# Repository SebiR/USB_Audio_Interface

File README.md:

# USB Audio Interface with Line In or Out
A very compact USB sound card with either two line inputs or two line outputs

## Features
* USB-C connector (USB 1.1 standard)
* Can be set to Line Out or Line In with solder jumpers
* The front plate can be flipped for Input or Output labeling
* Bus powered
* With PCB front plates no mechanical work is neccessary (except for some countersinking)

# Inner Workings

The main chip of the audio interface is a PCM2904 from Texas Instruments. It has an in- and output capability of 16bit at 48kHz, enough for most applications.
A high-quality OPA2523 op amp is used as a low-pass filter to get rid of high frequency noise. It's basically a copy of the PCM2902 eval board from TI.

On the underside, there are six SMT solder jumpers. Four of them determine the direction of the input/output LPF, so configuring the device as a Line In or a Line out device.
In case of a Line out configuration, the two inputs can be tied to GND to avoid any noise.

# Case

The PCB and the front plates are designed to fit inside ultra small Hammond 1455D601 metal case.
But if you want to save ~15€, you can download the 3D CAD files for the case and print it for yourself:
https://www.hammfg.com/part/1455D601

Although a nice anodized aluminum case is pretty nifty!

# Maybe?
It would be really nice to be able to change the direction mid-operation, but that would require some analog switches. Maybe I'll create another version somewhere in the future

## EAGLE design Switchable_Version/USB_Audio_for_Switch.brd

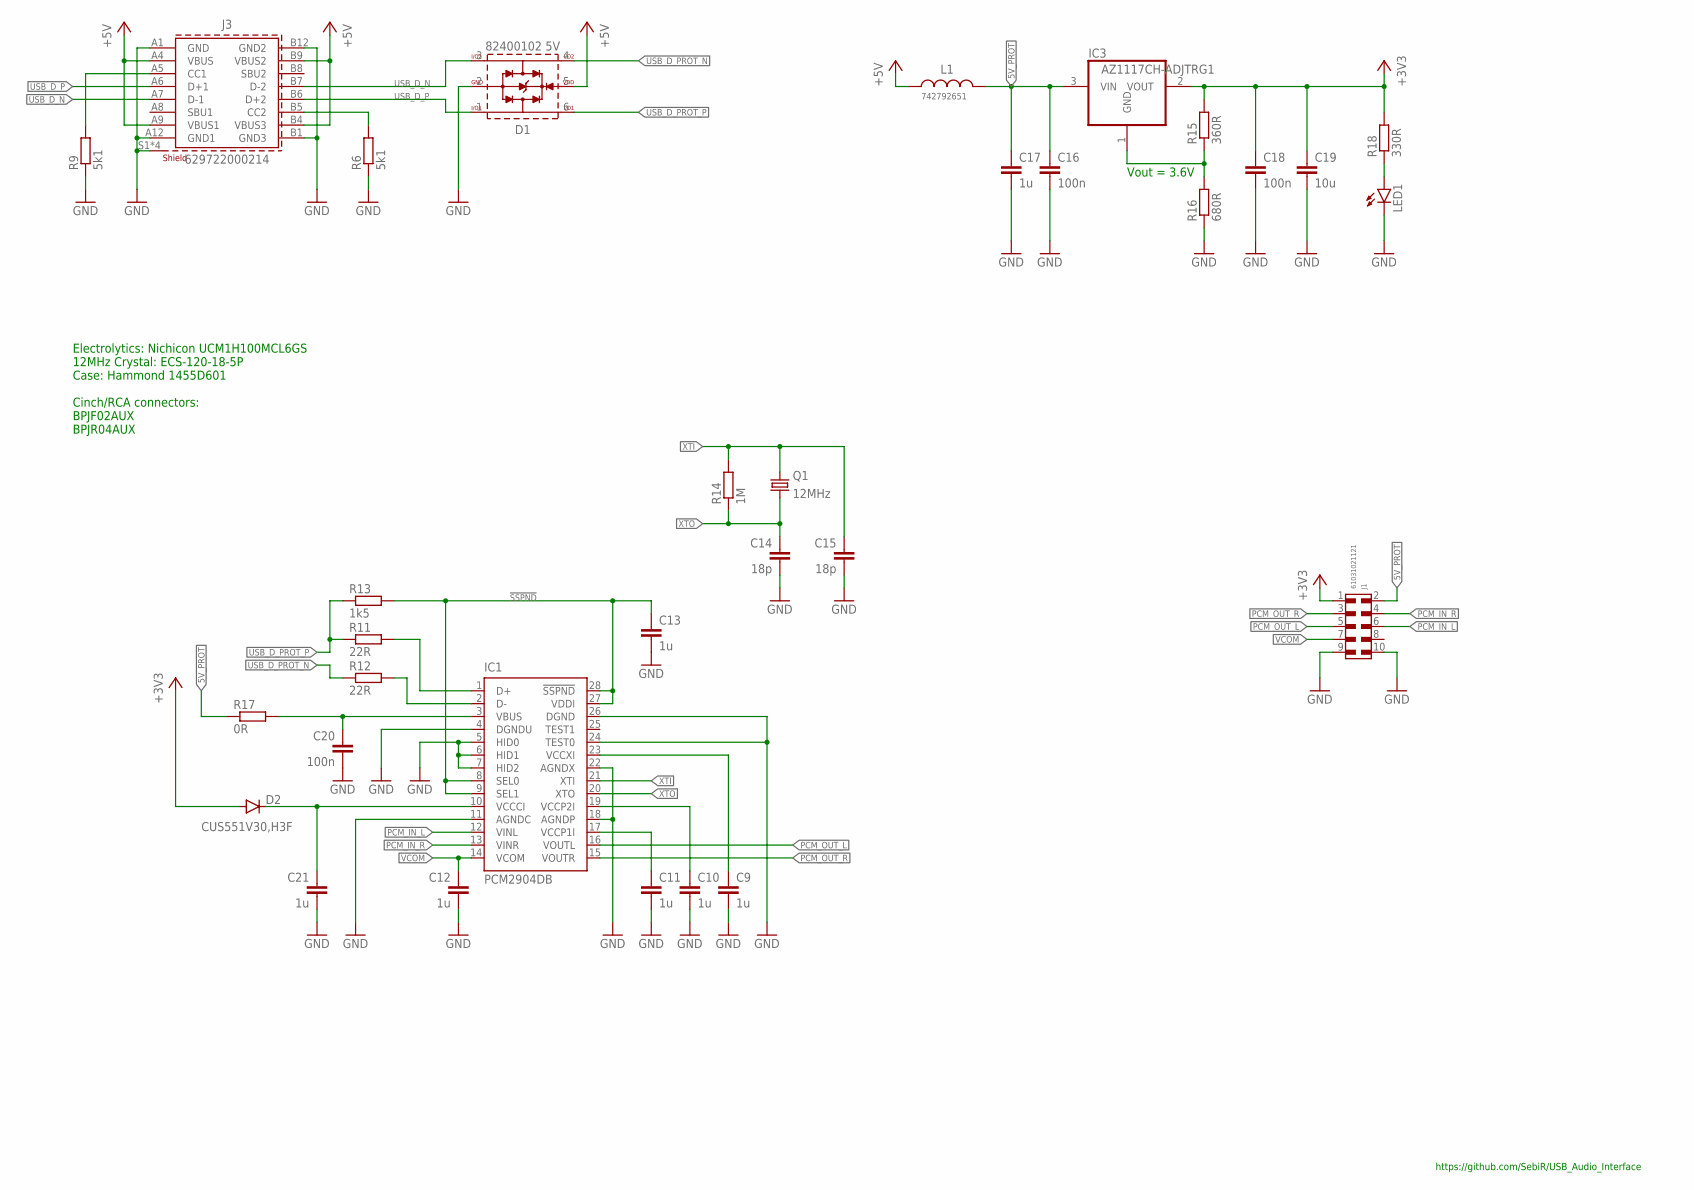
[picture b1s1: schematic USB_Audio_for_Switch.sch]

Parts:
C9, C10, C11, C12, C13, C17, C21: 1u; C0603
C14, C15: 18p; C0603
C16, C18, C20: 100n; C0603
C19: 10u; C0603
D1: 82400102 5V; WE-TVS_SOT23-6L
D2: CUS551V30,H3F; SOD323-R
IC1: PCM2904DB; SSOP28DB
IC3: AZ1117CH-ADJTRG1; SOT223
J1: 61031021121
J3: 629722000214
L1: 742792651; WE-CBF_0603_W2.6
LED1: LEDMICRO-SIDELED; MICRO-SIDELED
Q1: 12MHz; HC49UP
R6, R9: 5k1; R0603
R11, R12: 22R; R0603
R13: 1k5; R0603
R14: 1M; R0603
R15: 360R; R0603
R16: 680R; R0603
R17: 0R; R0603
R18: 330R; R0603

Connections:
5V_PROT: C16.1, C17.1, IC3.3 (VIN), J1.2, L1.2, R17.1
!SSPND: C13.1, IC1.8 (SEL0), IC1.9 (SEL1), IC1.27 (VDDI), IC1.28 (!SSPND), R13.2
+3V3: C18.1, C19.1, D2.A, IC3.2 (VOUT), J1.1, R15.2, R18.2
+5V: D1.5 (VDD), J3.A4 (VBUS), J3.A9 (VBUS1), J3.B4 (VBUS3), J3.B9 (VBUS2), L1.1
GND: C9.2, C10.2, C11.2, C12.2, C13.2, C14.2, C15.2, C16.2, C17.2, C18.2, C19.2, C20.2, C21.2, D1.2 (GND), IC1.4 (DGNDU), IC1.5 (HID0), IC1.6 (HID1), IC1.7 (HID2), IC1.11 (AGNDC), IC1.18 (AGNDP), IC1.22 (AGNDX), IC1.24 (TEST0), IC1.26 (DGND), J1.9, J1.10, J3.A1 (GND), J3.A12 (GND1), J3.B1 (GND3), J3.B12 (GND2), J3.S1 (SHIELD), J3.S2 (SHIELD), J3.S3 (SHIELD), J3.S4 (SHIELD), LED1.C, R6.1, R9.1, R16.1
unnamed: J3.A5 (CC1), R9.2
unnamed: J3.B5 (CC2), R6.2
unnamed: IC3.1 (GND), R15.1, R16.2
unnamed: LED1.A, R18.1
unnamed: C20.1, IC1.3 (VBUS), R17.2
unnamed: C9.1, IC1.23 (VCCXI)
unnamed: C11.1, IC1.17 (VCCP1I)
unnamed: C10.1, IC1.19 (VCCP2I)
unnamed: C21.1, D2.C, IC1.10 (VCCCI)
PCM_IN_L: IC1.12 (VINL), J1.6
PCM_IN_R: IC1.13 (VINR), J1.4
PCM_OUT_L: IC1.16 (VOUTL), J1.5
PCM_OUT_R: IC1.15 (VOUTR), J1.3
USB_D_N: D1.3 (I/O2), J3.A7 (D-1), J3.B7 (D-2)
USB_D_P: D1.1 (I/O1), J3.A6 (D+1), J3.B6 (D+2)
USB_D_PCM_N: IC1.2 (D-), R12.2
USB_D_PCM_P: IC1.1 (D+), R11.2
USB_D_PROT_N: D1.4 (I/O4), R12.1
USB_D_PROT_P: D1.6 (I/O3), R11.1, R13.1
VCOM: C12.1, IC1.14 (VCOM), J1.7
XTI: C15.1, IC1.21 (XTI), Q1.2, R14.2
XTO: C14.1, IC1.20 (XTO), Q1.1, R14.1

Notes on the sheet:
Electrolytics: Nichicon UCM1H100MCL6GS 12MHz Crystal: ECS-120-18-5P Case: Hammond 1455D601 Cinch/RCA connectors: BPJF02AUX BPJR04AUX
Vout = 3.6V
https://github.com/SebiR/USB_Audio_Interface

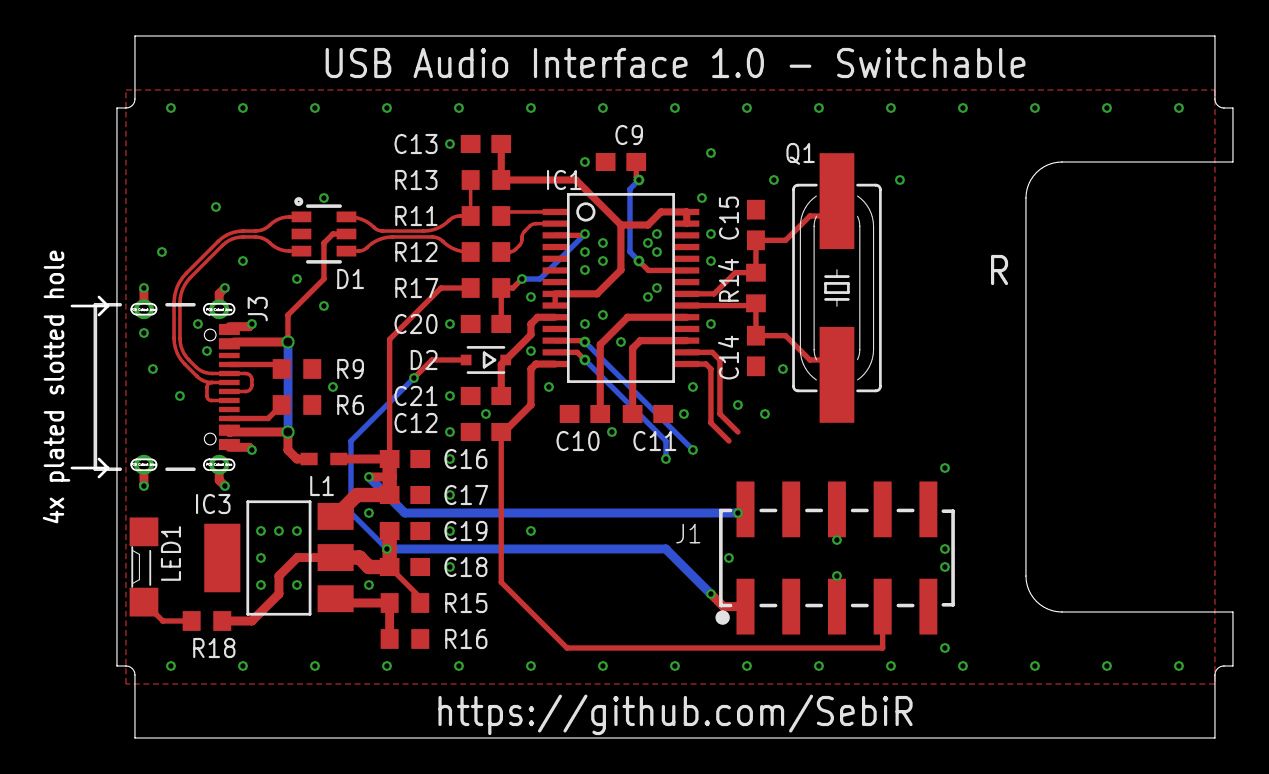
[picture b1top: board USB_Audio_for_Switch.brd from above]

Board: 2 copper layers, 66.3 x 38.8 mm, 32 parts (0 on the bottom side), 27 nets.

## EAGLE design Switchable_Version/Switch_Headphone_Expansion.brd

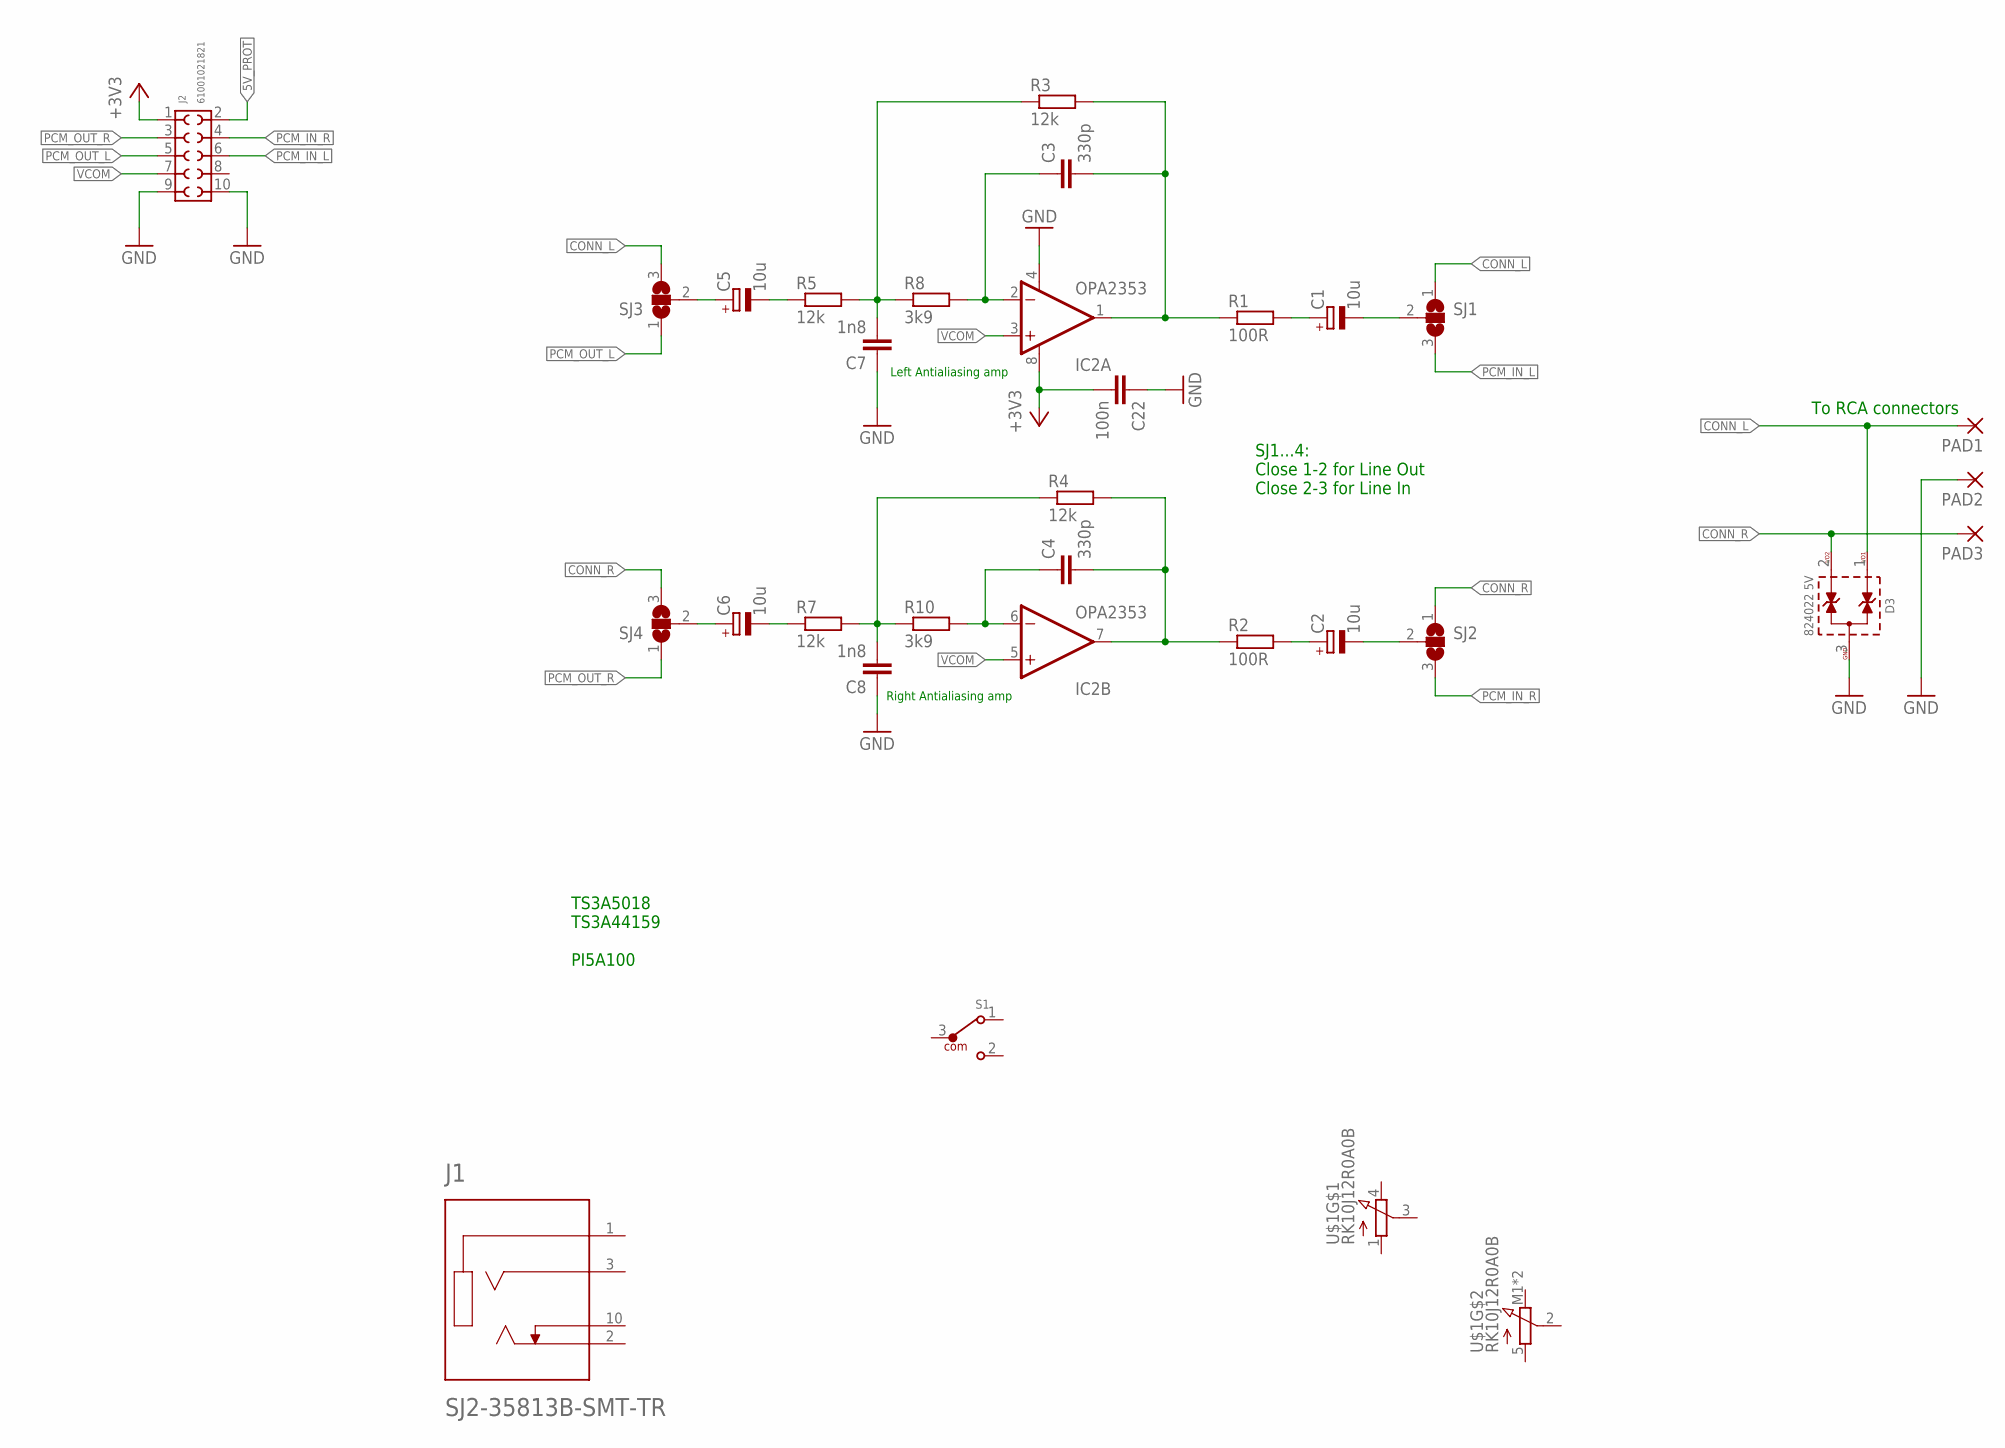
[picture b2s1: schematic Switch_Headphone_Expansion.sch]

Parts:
C1, C2, C5, C6: 10u; UD-4X5,8_NICHICON
C3, C4: 330p; C0603
C7, C8: 1n8; C0603
C22: 100n; C0603
D3: 824022 5V; WE-TVS_SOT23-3L
IC2: OPA2353; SO08
J1: SJ2-35813B-SMT-TR; CUI_SJ2-35813B-SMT-TR
J2: 61001021821
PAD1, PAD2, PAD3: 2,15/1,0
R1, R2: 100R; R0603
R3, R4, R5, R7: 12k; R0603
R8, R10: 3k9; R0603
S1: 450405020524
SJ1, SJ2, SJ3, SJ4: SJ2W; SJ_2
U$1: RK10J12R0A0B

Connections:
5V_PROT: J2.2
+3V3: C22.2, IC2.8 (V+), J2.1
CONN_L: D3.1 (I/O1), PAD1.1, SJ1.1, SJ3.3
CONN_R: D3.2 (I/O2), PAD3.1, SJ2.1, SJ4.3
GND: C7.1, C8.1, C22.1, D3.3 (GND), IC2.4 (V-), J2.9, PAD2.1
unnamed: C3.2, IC2.1 (OUT), R1.1, R3.2
unnamed: C4.2, IC2.7 (OUT), R2.1, R4.2
unnamed: C3.1, IC2.2 (-IN), R8.2
unnamed: C7.2, R3.1, R5.2, R8.1
unnamed: C5.-, R5.1
unnamed: C1.+, R1.2
unnamed: C2.+, R2.2
unnamed: C4.1, IC2.6 (-IN), R10.2
unnamed: C8.2, R4.1, R7.2, R10.1
unnamed: C6.-, R7.1
unnamed: C5.+, SJ3.2
unnamed: C6.+, SJ4.2
unnamed: C1.-, SJ1.2
unnamed: C2.-, SJ2.2
PCM_IN_L: J2.6, SJ1.3
PCM_IN_R: J2.4, SJ2.3
PCM_OUT_L: J2.5, SJ3.1
PCM_OUT_R: J2.3, SJ4.1
VCOM: IC2.3 (+IN), IC2.5 (+IN), J2.7

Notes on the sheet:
Right Antialiasing amp
Left Antialiasing amp
SJ1...4: Close 1-2 for Line Out Close 2-3 for Line In
TS3A5018 TS3A44159 PI5A100
To RCA connectors

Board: 2 copper layers, 30 parts (0 on the bottom side), 23 nets, no tracks yet.

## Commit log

2024-01-12 * Cleaned schematic a bit, exported new PDF * Cleaned up the PCB, USB has now its own netclass, updated GERBER * Updated image of PCB * Updated readme
2024-01-12 * Fixed layout, two airwires on the USB removed
2024-01-12 Updated tValue positions for easy population
2024-01-12 Added population plan
2024-01-25 Started on switchable version. Moved EAGLE files into individual folders
2024-02-10 Added actual images of the PCBA

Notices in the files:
parts and their libraries:
Wurth_Switch_WS-SLSU: Copyright: Würth Elektronik
